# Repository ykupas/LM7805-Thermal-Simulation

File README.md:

# PCB Thermal Simulation
PCB layout thermal simulation using [ElmerFEM](https://github.com/elmercsc/elmerfem) and [PoeAlex KiCAD-Thermal-Sim](https://github.com/PoeAlex/KiCad_Thermal_Sim) repository. 

## Used Tools
* [KiCAD](https://www.kicad.org/) v10.0.7
* [FreeCAD](https://www.freecad.org/) v1.1.4
* [Paraview](https://www.paraview.org/) 6.2.0

# Main Goal
Simulate and analyze the thermal characteristics of a simple LM7805 circuit, with a 12 V input, 5 V output, and load currents of 0.5 A and 1 A, using different configurations of the TO-220 package. After the simulation, validate using practical examples.

# Circuit
Circuit characteristics and thermal assumptions are presented below.

## Schematic

## PCB Layout

## Thermal Characteristics

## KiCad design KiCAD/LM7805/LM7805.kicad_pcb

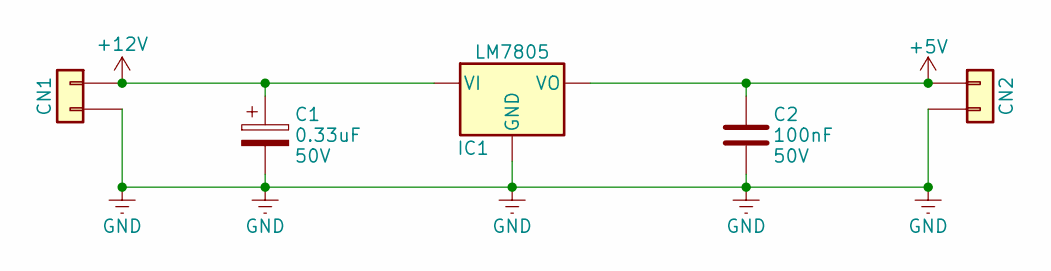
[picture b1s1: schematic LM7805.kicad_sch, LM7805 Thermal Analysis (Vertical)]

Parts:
C1: 0.33uF; CP_Radial_D5.0mm_P2.00mm; Voltage 50V
C2: 100nF; C_Disc_D5.0mm_W2.5mm_P5.00mm; Voltage 50V
CN1, CN2: Conn_01x02; PinHeader_1x02_P2.54mm_Vertical
IC1: LM7805; TO-220-3_Vertical

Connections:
+5V: C2.1, CN2.1, IC1.3 (VO)
+12V: C1.1, CN1.1, IC1.1 (VI)
GND: C1.2, C2.2, CN1.2, CN2.2, IC1.2 (GND)

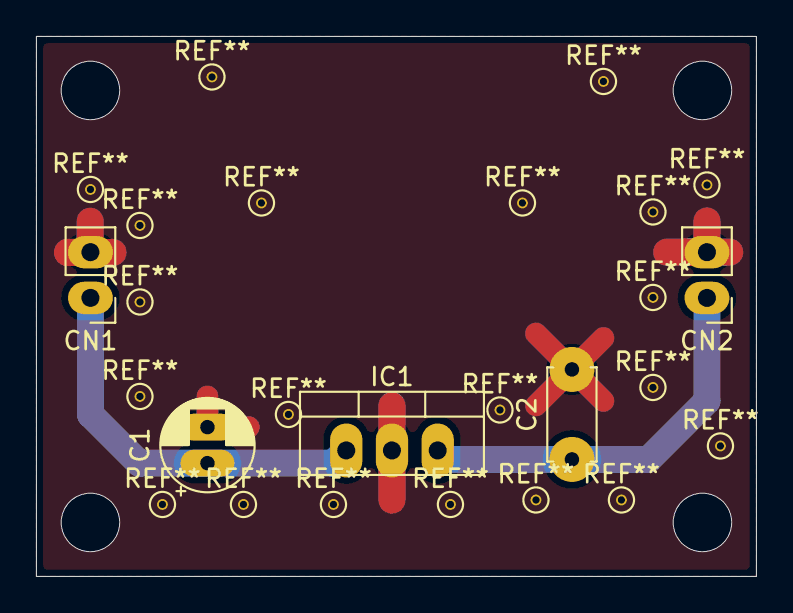
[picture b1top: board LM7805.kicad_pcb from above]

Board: 2 copper layers, 40.0 x 30.0 mm, 5 parts (0 on the bottom side), 3 nets.
